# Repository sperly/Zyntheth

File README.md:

# Zynthethet
The Zyntheth will be a 4-6 operator 16 voices FM synthesis synth. It will have DIN-5 MIDI In, Thru and Out (from the Arpeggio). It will also have a USB-based Midi interface. There will also be support for Ethernet based RTP-MIDI.

It will have a stereo output (3.5mm plug) and it is powered by a regular micro-USB phone charger (500mA is enough). The user interface is a 3.5 inch touch LCD and 5 rotary encoders.

# Hardware
The hardware consists of 5 different pcb's:

The power board, takes the power from the micro-USB and converts it to 3.3v for other modules to run on.
The UI board, has the display and a connection for 1 encoder board with 5 encoders. It also has a Teensy 4.1 micro controller with 8Mb extra flash for graphics.
The Audio board, is the audio generator board with a Teensy 4.1 with 16Mb added PSRAM for additional effects usage.
The Interface board, has an Teensy 4.1 with ethernet interface added. This board takes care of all signals in and out from the Zyntheth (apart from the audio signals). It will also take care of arpeggio note generation.
Encoder board, a board with 5 rotary encoder and a button fitted to it. It has a SPI interface connection to the UI board.

# Functionality
4-6 operators (similar to DX9/DX7) FM synthesis in multiple algorithmic configuration
Individual envelope for each operator
Configurable detune, volume, panning for each operator
General envelope
Filter, 5-band parametric equlizer
Multiple effects: chorus, reverb, echo/delay, BitChrusher, Granular, etc.
Dual configurable LFO, either frequency, detune och volume
Configurable midi channel

# Todo
Add USB Audio output.

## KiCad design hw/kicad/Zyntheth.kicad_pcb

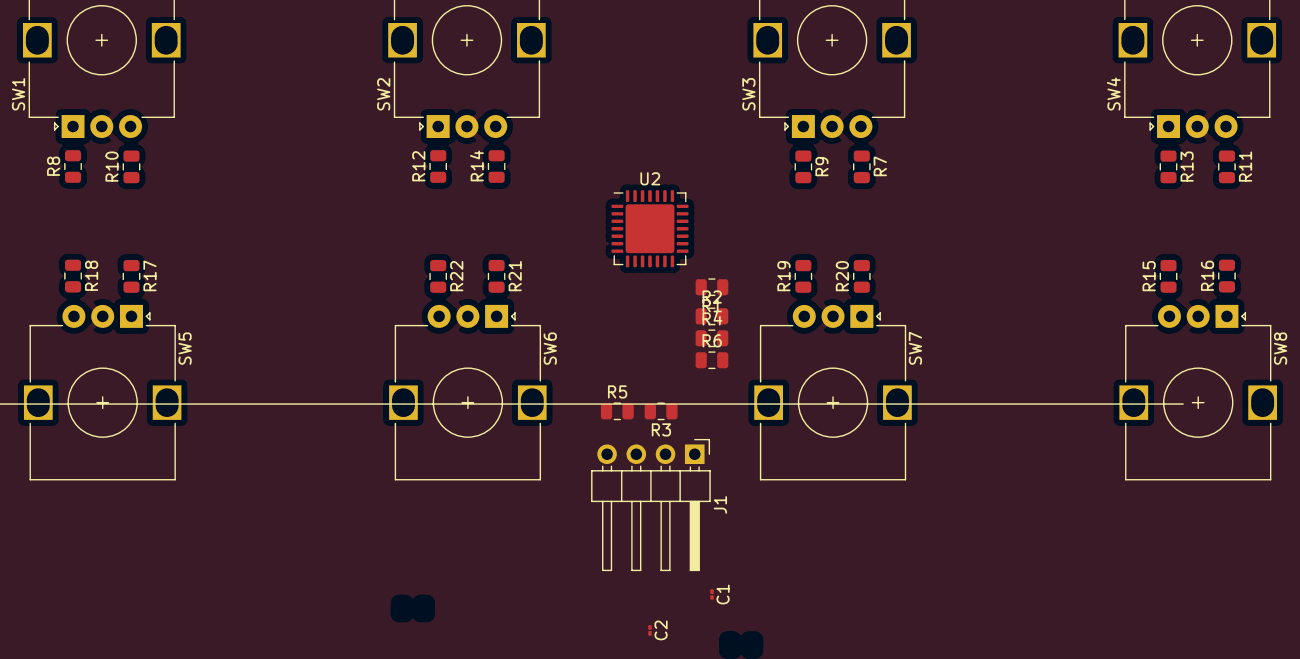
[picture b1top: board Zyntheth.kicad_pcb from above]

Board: 2 copper layers, 34 parts (0 on the bottom side), 24 nets, no tracks yet.

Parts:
C1: 0.1µF; C_01005_0402Metric
C2: 10nF; C_01005_0402Metric
J1: Conn_01x04_Female; PinHeader_1x04_P2.54mm_Horizontal
R1, R2, R3, R4, R5, R6, R7, R8, R9, R10, R11, R12, R13, R14, R15, R16, R17, R18, R19, R20, R21, R22: R; R_0805_2012Metric
SW1, SW2, SW3, SW4, SW5, SW6, SW7, SW8: Rotary_Encoder; RotaryEncoder_Alps_EC12E_Vertical_H20mm
U2: MCP23017_ML; QFN-28-1EP_6x6mm_P0.65mm_EP4.25x4.25mm

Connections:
+3V3: C1.1, C2.1, J1.1, R1.1, R3.1, R5.1, R7.2, R8.1, R9.2, R10.1, R11.2, R12.1, R13.2, R14.1, R15.2, R16.2, R17.1, R18.1, R19.2, R20.2, R21.1, R22.1, U2.5
GND: C1.2, C2.2, J1.4, R2.2, R4.2, R6.2, SW1.C, SW2.C, SW3.C, SW4.C, SW5.C, SW6.C, SW7.C, SW8.C, U2.6, U2.29
unnamed: J1.2, R3.2, U2.9
unnamed: J1.3, R5.2, U2.8
unnamed: R1.2, U2.14
unnamed: R2.1, U2.13
unnamed: R4.1, U2.12
unnamed: R6.1, U2.11
unnamed: R7.1, SW3.B, U2.18
unnamed: R8.2, SW1.A, U2.25
unnamed: R9.1, SW3.A, U2.17
unnamed: R10.2, SW1.B, U2.26
unnamed: R11.1, SW4.B, U2.22
unnamed: R12.2, SW2.A, U2.1
unnamed: R13.1, SW4.A, U2.21
unnamed: R14.2, SW2.B, U2.2
unnamed: R15.1, SW8.B, U2.24
unnamed: R16.1, SW8.A, U2.23
unnamed: R17.2, SW5.A, U2.27
unnamed: R18.2, SW5.B, U2.28
unnamed: R19.1, SW7.B, U2.20
unnamed: R20.1, SW7.A, U2.19
unnamed: R21.2, SW6.A, U2.3
unnamed: R22.2, SW6.B, U2.4

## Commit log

2020-06-04 Added sirst draft of kicad schematics
2021-05-31 Added EncoderBoard designs and initial software projects
2021-06-02 Added menuhandler with submenu functionality.
2021-06-03 Added MidiBoard plans. Added filter menu (ADSR).
2021-06-03 Added stuff to gitignore. Added driver for IL9341_t3
2021-06-03 Added Makefile to .gitignore
2021-06-04 Added UIBoard (rev 1.1)
    Updated .gitignore to inklude picknPlace and BOM for boards
    Added Metro and an updated IL9341 library.
2021-06-04 Added FlexCAN as submodule
2021-06-04 Added Bounce2 as submodule
2021-06-04 Added Metro as submodule
2021-06-04 Removed submodule Software/zyntheth-controller/lib/Metro
2021-06-04 Removed submodule Software/zyntheth-controller/lib/spi4teensy3
2021-06-05 Updated log handling, added waveform imaged, started on communictions
2021-06-08 Added Power and Audio boards
    Moved valuecontainer initialization to class.
2021-06-09 added .c and .h files for libs to .gitignore
2021-06-09 Added some libs
2021-06-14 Added button gfx.
    Cleanup in libs and added touch.
2021-06-14 Added STL version of all OBJ files, removed OBJ-zips
2021-06-14 Added system-dwesign
2021-06-14 Added Zyntheth.png
2021-06-14 Added Zyntheth.png background
2023-12-17 Updates to code base
